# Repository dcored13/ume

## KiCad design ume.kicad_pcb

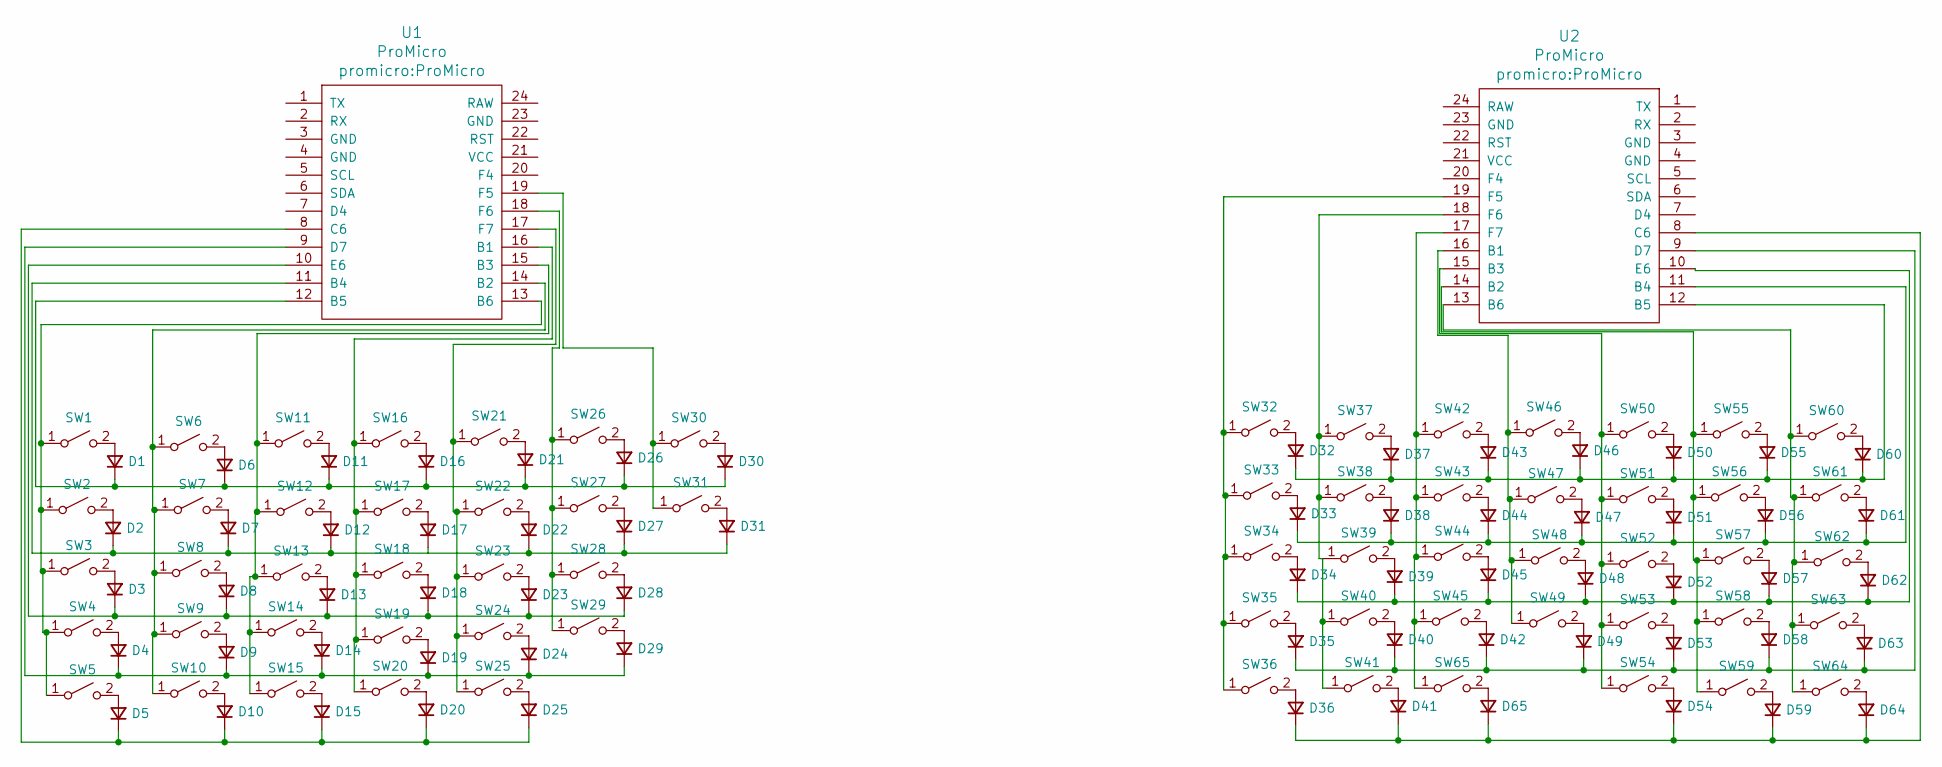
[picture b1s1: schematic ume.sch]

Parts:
D1, D2, D3, D4, D5, D6, D7, D8, D9, D10, D11, D12, D13, D14, D15, D16, D17, D18, D19, D20, D21, D22, D23, D24, D25, D26, D27, D28, D29, D30, D31, D32, D33, D34, D35, D36, D37, D38, D39, D40, D41, D42, D43, D44, D45, D46, D47, D48, D49, D50, D51, D52, D53, D54, D55, D56, D57, D58, D59, D60, D61, D62, D63, D64, D65: D_Small; D_T-1_P5.08mm_Horizontal
SW1, SW2, SW3, SW4, SW5, SW6, SW7, SW8, SW9, SW10, SW11, SW12, SW13, SW14, SW15, SW16, SW17, SW18, SW19, SW20, SW21, SW22, SW23, SW24, SW25, SW26, SW27, SW28, SW29, SW30, SW31, SW32, SW33, SW34, SW35, SW36, SW37, SW38, SW39, SW40, SW41, SW42, SW43, SW44, SW45, SW46, SW47, SW48, SW49, SW50, SW51, SW52, SW53, SW54, SW55, SW56, SW57, SW58, SW59, SW60, SW61, SW62, SW63, SW64, SW65: SW_SPST; SW_Cherry_MX_PCB_1.00u
U1, U2: ProMicro

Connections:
unnamed: D1.1 (K), D6.1 (K), D11.1 (K), D16.1 (K), D21.1 (K), D26.1 (K), D30.1 (K), U1.12 (B5)
unnamed: D1.2 (A), SW1.2 (B)
unnamed: D2.2 (A), SW2.2 (B)
unnamed: D3.2 (A), SW3.2 (B)
unnamed: D4.2 (A), SW4.2 (B)
unnamed: D5.2 (A), SW5.2 (B)
unnamed: D6.2 (A), SW6.2 (B)
unnamed: D7.2 (A), SW7.2 (B)
unnamed: D8.2 (A), SW8.2 (B)
unnamed: D9.2 (A), SW9.2 (B)
unnamed: D5.1 (K), D10.1 (K), D15.1 (K), D20.1 (K), D25.1 (K), U1.8 (C6)
unnamed: D10.2 (A), SW10.2 (B)
unnamed: D11.2 (A), SW11.2 (B)
unnamed: D2.1 (K), D7.1 (K), D12.1 (K), D17.1 (K), D22.1 (K), D27.1 (K), D31.1 (K), U1.11 (B4)
unnamed: D12.2 (A), SW12.2 (B)
unnamed: D3.1 (K), D8.1 (K), D13.1 (K), D18.1 (K), D23.1 (K), D28.1 (K), U1.10 (E6)
unnamed: D13.2 (A), SW13.2 (B)
unnamed: D4.1 (K), D9.1 (K), D14.1 (K), D19.1 (K), D24.1 (K), D29.1 (K), U1.9 (D7)
unnamed: D14.2 (A), SW14.2 (B)
unnamed: D15.2 (A), SW15.2 (B)
unnamed: D16.2 (A), SW16.2 (B)
unnamed: D17.2 (A), SW17.2 (B)
unnamed: D18.2 (A), SW18.2 (B)
unnamed: D19.2 (A), SW19.2 (B)
unnamed: D20.2 (A), SW20.2 (B)
unnamed: D21.2 (A), SW21.2 (B)
unnamed: D22.2 (A), SW22.2 (B)
unnamed: D23.2 (A), SW23.2 (B)
unnamed: D24.2 (A), SW24.2 (B)
unnamed: D25.2 (A), SW25.2 (B)
unnamed: D26.2 (A), SW26.2 (B)
unnamed: D27.2 (A), SW27.2 (B)
unnamed: D28.2 (A), SW28.2 (B)
unnamed: D29.2 (A), SW29.2 (B)
unnamed: D30.2 (A), SW30.2 (B)
unnamed: D31.2 (A), SW31.2 (B)
unnamed: D32.1 (K), D37.1 (K), D43.1 (K), D46.1 (K), D50.1 (K), D55.1 (K), D60.1 (K), U2.12 (B5)
unnamed: D32.2 (A), SW32.2 (B)
unnamed: D33.1 (K), D38.1 (K), D44.1 (K), D47.1 (K), D51.1 (K), D56.1 (K), D61.1 (K), U2.11 (B4)
unnamed: D33.2 (A), SW33.2 (B)
unnamed: D34.1 (K), D39.1 (K), D45.1 (K), D48.1 (K), D52.1 (K), D57.1 (K), D62.1 (K), U2.10 (E6)
unnamed: D34.2 (A), SW34.2 (B)
unnamed: D35.1 (K), D40.1 (K), D42.1 (K), D49.1 (K), D53.1 (K), D58.1 (K), D63.1 (K), U2.9 (D7)
unnamed: D35.2 (A), SW35.2 (B)
unnamed: D36.1 (K), D41.1 (K), D54.1 (K), D59.1 (K), D64.1 (K), D65.1 (K), U2.8 (C6)
unnamed: D36.2 (A), SW36.2 (B)
unnamed: D37.2 (A), SW37.2 (B)
unnamed: D38.2 (A), SW38.2 (B)
unnamed: D39.2 (A), SW39.2 (B)
unnamed: D40.2 (A), SW40.2 (B)
unnamed: D41.2 (A), SW41.2 (B)
unnamed: D42.2 (A), SW45.2 (B)
unnamed: D43.2 (A), SW42.2 (B)
unnamed: D44.2 (A), SW43.2 (B)
unnamed: D45.2 (A), SW44.2 (B)
unnamed: D46.2 (A), SW46.2 (B)
unnamed: D47.2 (A), SW47.2 (B)
unnamed: D48.2 (A), SW48.2 (B)
unnamed: D49.2 (A), SW49.2 (B)
unnamed: D50.2 (A), SW50.2 (B)
unnamed: D51.2 (A), SW51.2 (B)
unnamed: D52.2 (A), SW52.2 (B)
unnamed: D53.2 (A), SW53.2 (B)
unnamed: D54.2 (A), SW54.2 (B)
unnamed: D55.2 (A), SW55.2 (B)
unnamed: D56.2 (A), SW56.2 (B)
unnamed: D57.2 (A), SW57.2 (B)
unnamed: D58.2 (A), SW58.2 (B)
unnamed: D59.2 (A), SW59.2 (B)
unnamed: D60.2 (A), SW60.2 (B)
unnamed: D61.2 (A), SW61.2 (B)
unnamed: D62.2 (A), SW62.2 (B)
unnamed: D63.2 (A), SW63.2 (B)
unnamed: D64.2 (A), SW64.2 (B)
unnamed: D65.2 (A), SW65.2 (B)
unnamed: SW1.1 (A), SW2.1 (A), SW3.1 (A), SW4.1 (A), SW5.1 (A), U1.13 (B6)
unnamed: SW6.1 (A), SW7.1 (A), SW8.1 (A), SW9.1 (A), SW10.1 (A), U1.14 (B2)
unnamed: SW11.1 (A), SW12.1 (A), SW13.1 (A), SW14.1 (A), SW15.1 (A), U1.15 (B3)
unnamed: SW16.1 (A), SW17.1 (A), SW18.1 (A), SW19.1 (A), SW20.1 (A), U1.16 (B1)
unnamed: SW21.1 (A), SW22.1 (A), SW23.1 (A), SW24.1 (A), SW25.1 (A), U1.17 (F7)
unnamed: SW26.1 (A), SW27.1 (A), SW28.1 (A), SW29.1 (A), U1.18 (F6)
unnamed: SW30.1 (A), SW31.1 (A), U1.19 (F5)
unnamed: SW32.1 (A), SW33.1 (A), SW34.1 (A), SW35.1 (A), SW36.1 (A), U2.19 (F5)
unnamed: SW37.1 (A), SW38.1 (A), SW39.1 (A), SW40.1 (A), SW41.1 (A), U2.18 (F6)
unnamed: SW42.1 (A), SW43.1 (A), SW44.1 (A), SW45.1 (A), SW65.1 (A), U2.17 (F7)
unnamed: SW46.1 (A), SW47.1 (A), SW48.1 (A), SW49.1 (A), U2.16 (B1)
unnamed: SW50.1 (A), SW51.1 (A), SW52.1 (A), SW53.1 (A), SW54.1 (A), U2.15 (B3)
unnamed: SW55.1 (A), SW56.1 (A), SW57.1 (A), SW58.1 (A), SW59.1 (A), U2.14 (B2)
unnamed: SW60.1 (A), SW61.1 (A), SW62.1 (A), SW63.1 (A), SW64.1 (A), U2.13 (B6)

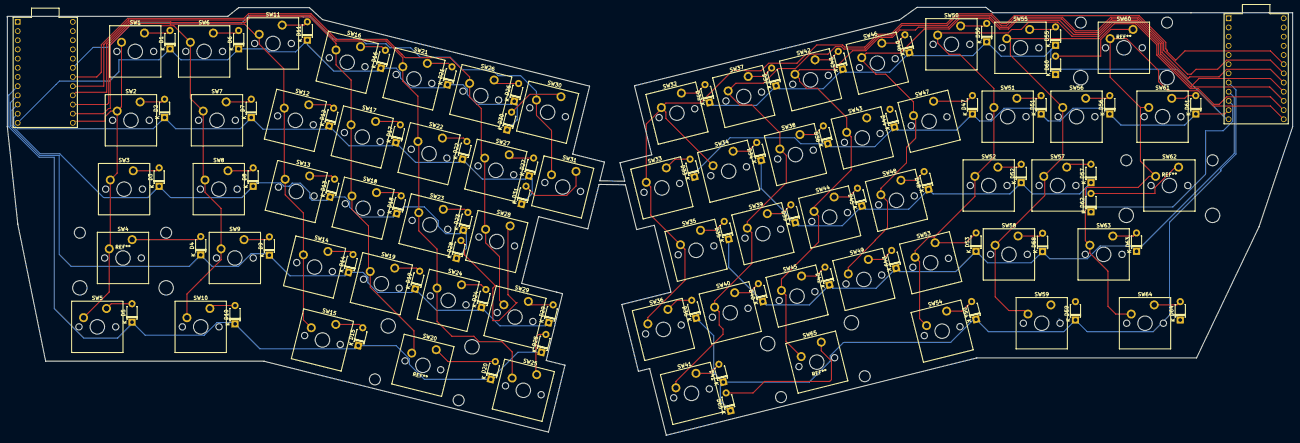
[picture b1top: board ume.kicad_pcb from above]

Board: 2 copper layers, 355.6 x 118.4 mm, 132 parts (0 on the bottom side), 89 nets.
